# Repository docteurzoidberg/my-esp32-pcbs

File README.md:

# my-esp32-pcbs
This repository regroups all of my custom esp32 pcbs. These pcbs are meant to be generic and usable in a large panel of projects.
## espBreakout

Breakout board for 38 pins esp32.
- Configurable power distribution (3.3V/5V)
- 6 phoenix-style connectors for i/o  
Last revision: v1.1

## espBreakout-adc-module

I2C extension for the espBreakout
- 2x 4 channels adc (ax)
- 8 phoenix-style connectors for i/o
Last revision: WIP

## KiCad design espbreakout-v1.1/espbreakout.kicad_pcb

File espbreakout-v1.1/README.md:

# espbreakout

Breakout board for 38 pins esp32.

## ESP32 versions

- I worked with az-delivery esp32 boards.  
**links**

## Pictures

//todo

## Features

- 6 Phoenix connectors (3 pins, 3.81mm pitch) to use with prewired GPIOS or custom ones
- choosable power (3 or 5V) for each Phoenix connector
- JST-PH 2mm style 5 pins connector for I2C (providing both 3.3 and 5V power)
- JST-PH 2mm style 5 pins connector for SERIAL
- 3 SMD LEDs to use with prewired configuration or custom GPIOs
- global board GND among all connectors

## Power distribution

- Each phoenix connector got a (+) pin that can be either tied to 3v or 5v rail. The desired voltage can be connected to the phoenix connector through a solder jumper.

- Each phoenix connector got a GND pin linked to global board GND.

## LEDs

3 SMD LEDs placeholders are included, you are free to use them.
Each LED have a solder jumper, and a resistor placeholder next to it.

- LED1 can be tied to 5V rail through solder jumper.

- LED2 can be tied to GPIO32 through solder jumper.

- LED3 can be tied to GPIO4 through solder jumper.

Please, beware of choosing the right resistor for either 5V or 3V power GPIOs, depending on your solder jumper setup!

## Data

- J1 data pin can be tied (actually nothing. needs to be fixed...) when solder jumper closed

- J2 data pin can be tied to GPIO25 through solder jumper.

- J3 data pin can be tied to GPIO5 through solder jumper.

- J4 data pin can be tied to GPIO26 through solder jumper.

- J5 data pin can be tied to GPIO33 through solder jumper.

- J6 data pin can be tied to GPIO32* through solder jumper.

*J6 data pin and LED2 can be tied on the same pin (GPIO32). This is expected behavior.  
I'm using this output for a relay and the led reflects its status.

When the solder jumper of a data pin is not connected, you are free to tied it to any pin on the esp. A simple wire to the pad next to the ESP's pin does the job.

//todo pictures of custom pin mapping

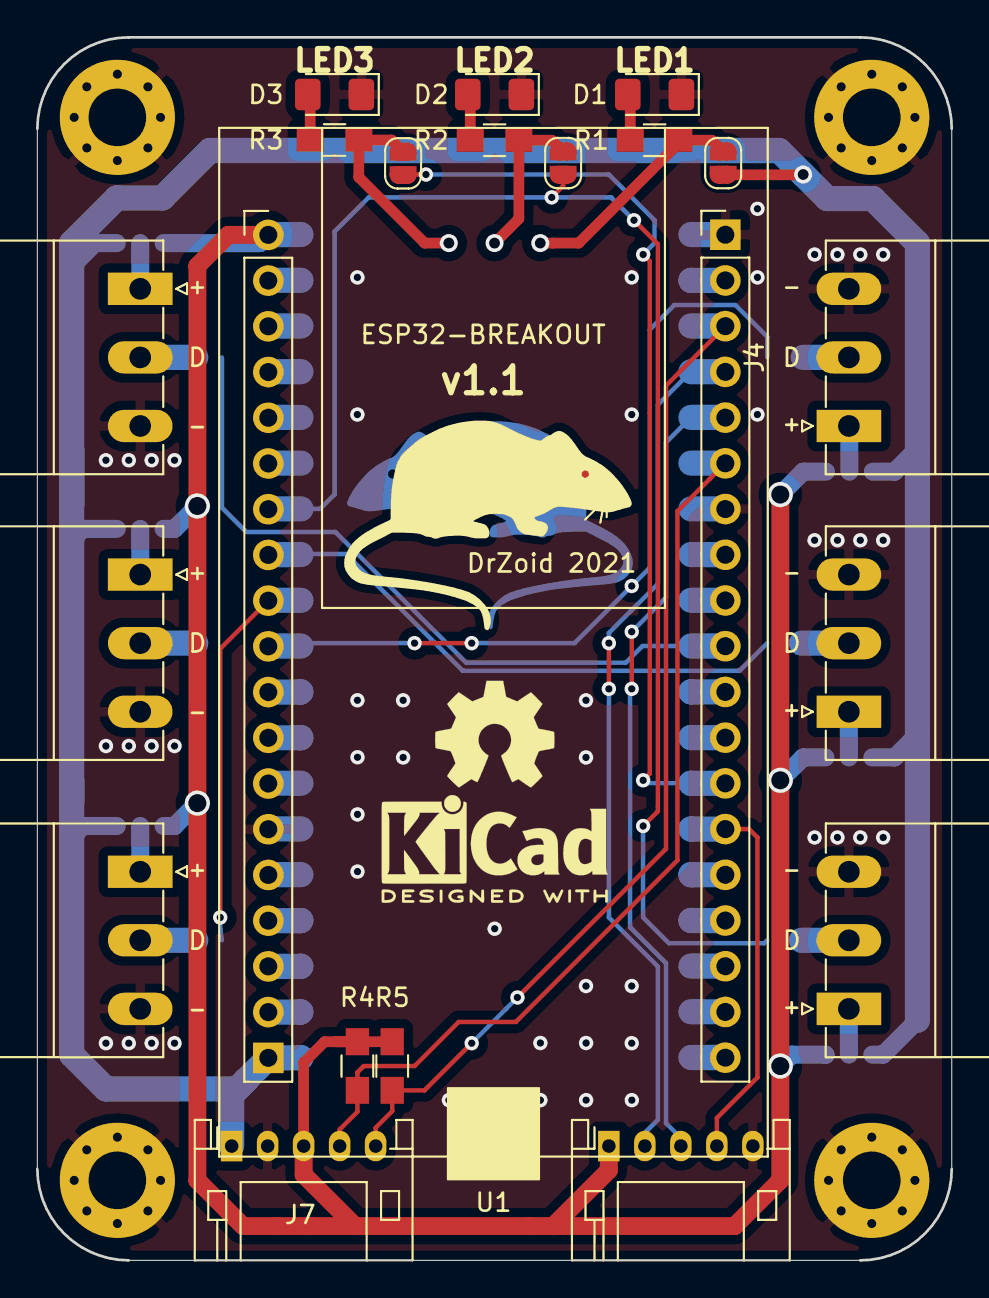
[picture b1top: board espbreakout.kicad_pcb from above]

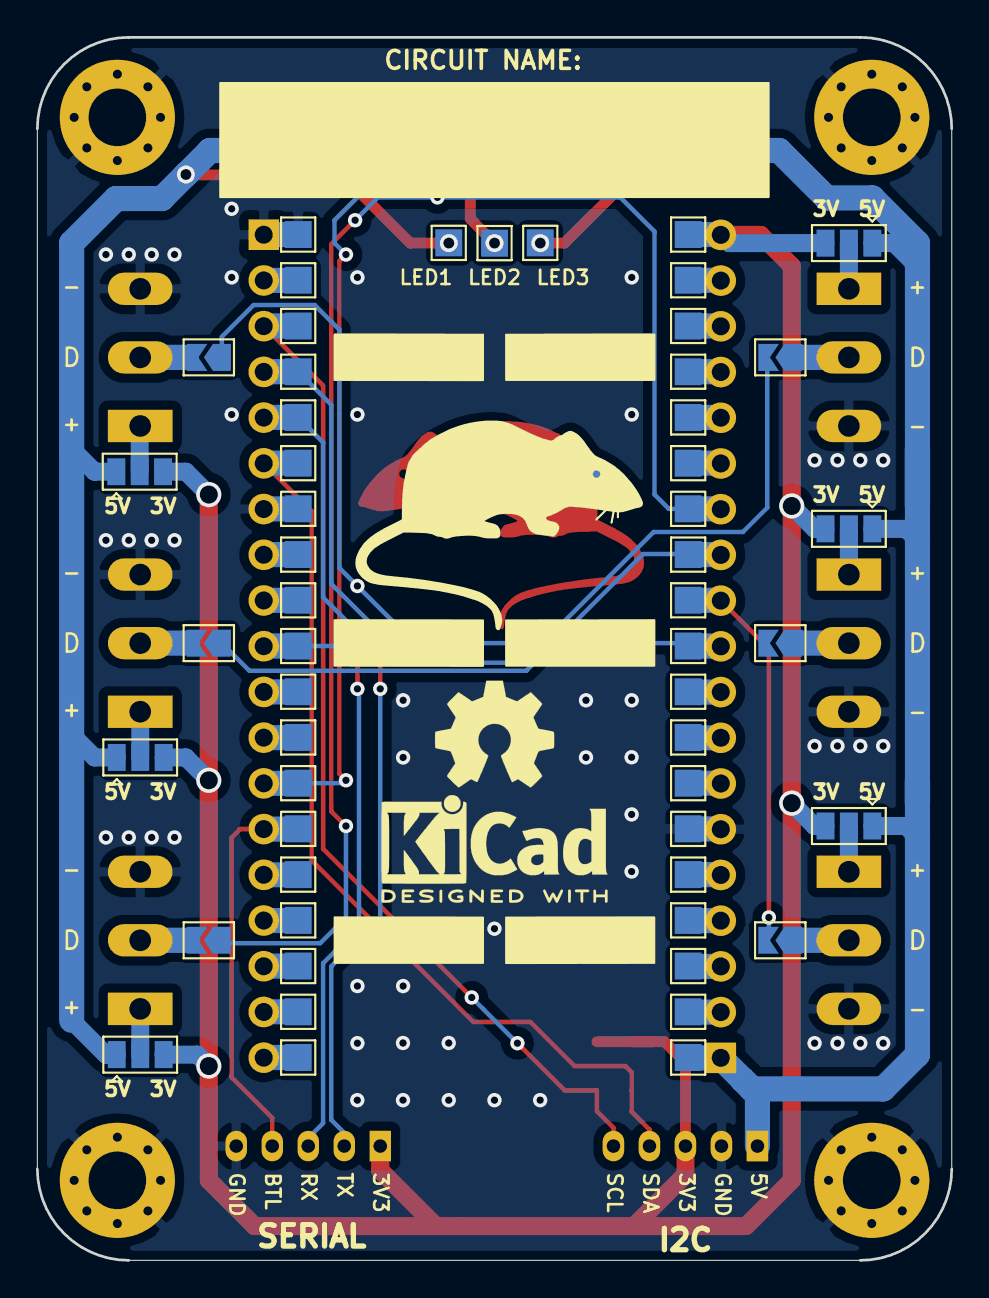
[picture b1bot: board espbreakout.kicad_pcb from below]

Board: 2 copper layers, 50.8 x 67.9 mm, 36 parts (12 on the bottom side), 32 nets.

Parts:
D1: POWER; LED_1206_3216Metric_Pad1.42x1.75mm_HandSolder
D2, D3: RELAY; LED_1206_3216Metric_Pad1.42x1.75mm_HandSolder
H1, H2, H3, H4: MountingHole_Pad; MountingHole_3.2mm_M3_Pad_Via
J1: TEMPERATURE; PhoenixContact_MC-G_03x3.81mm_Angled
J2: LED DATA; PhoenixContact_MC-G_03x3.81mm_Angled
J3: UNK; PhoenixContact_MC-G_03x3.81mm_Angled
J4: POWER; PhoenixContact_MC-G_03x3.81mm_Angled
J5: CURRENT; PhoenixContact_MC-G_03x3.81mm_Angled
J6: RELAY; PhoenixContact_MC-G_03x3.81mm_Angled
J7: I2C; JST_PH_S5B-PH-K_05x2.00mm_Angled
J8: SERIAL; JST_PH_S5B-PH-K_05x2.00mm_Angled
JP1, JP2, JP15: PLJP; SolderJumper-2_P1.3mm_Open_RoundedPad1.0x1.5mm
JP3, JP5, JP14: SolderJumper_2_Open; SolderJumper-2_P1.3mm_Open_TrianglePad1.0x1.5mm
JP4, JP6, JP7: D; SolderJumper-2_P1.3mm_Open_TrianglePad1.0x1.5mm
JP8, JP9, JP10, JP11, JP12, JP13: Jumper_3_Open; SolderJumper-3_P1.3mm_Open_Pad1.0x1.5mm
R1: 150; R_0805_HandSoldering
R2, R3: 51; R_0805_HandSoldering
R4, R5: 4.7K; R_0805_HandSoldering
U1: ESP32-38pins; esp32 38pin azdelivery

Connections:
3V3: J7.3, J8.1, JP8.3, JP9.3, JP10.3, JP11.3, JP12.3, JP13.3, R4.1, R5.1, U1.1
5V: J7.1, JP1.2, JP8.1, JP9.1, JP10.1, JP11.1, JP12.1, JP13.1, U1.19
CURRENT_SENSOR: JP6.1, U1.8
GND: D1.1, D2.1, D3.1, H1.1, H2.1, H3.1, H4.1, J1.3, J2.3, J3.3, J4.3, J5.3, J6.3, J7.2, J8.5, U1.14, U1.20, U1.26
GPIO0: J8.4, U1.33
GPIO4: JP15.2, U1.32
GPIO5: JP14.2, U1.29
GPIO26: JP4.1, U1.10
LED_DATA: JP5.2, U1.9
unnamed: D1.2, R1.2
unnamed: D2.2, R2.2
unnamed: D3.2, R3.2
unnamed: J1.1, JP8.2
unnamed: J1.2, JP3.1
unnamed: J2.1, JP11.2
unnamed: J2.2, JP5.1
unnamed: J3.1, JP13.2
unnamed: J3.2, JP14.1
unnamed: J4.1, JP9.2
unnamed: J4.2, JP4.2
unnamed: J5.1, JP10.2
unnamed: J5.2, JP6.2
unnamed: J6.1, JP12.2
unnamed: J6.2, JP7.2
unnamed: JP1.1, R1.1
unnamed: JP2.1, R2.1
unnamed: JP15.1, R3.1
RELAY_TRIGGER: JP2.2, JP7.1, U1.7
RX: J8.3, U1.24
SCL: J7.5, R5.2, U1.22
SDA: J7.4, R4.2, U1.25
TX: J8.2, U1.23

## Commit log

2021-01-23 release
2021-01-23 add v.10 board
2021-01-23 easpbreakout adc module wip
2021-01-23 readme
2021-01-26 reading and clarifying
2021-01-29 espbreakout v1.0 for eurotrash and jesserockz
2021-01-29 espbreakout v1.0 move
